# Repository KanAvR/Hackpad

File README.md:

# Hackpad

Hackpad is a 9 key macropad with a rotary encoder, an OLED Display and uses KMK firmware.

This will be used as a macropad for common desktop shortcuts such as, switching desktops; To boost productivity.

## Features:
- Open case because it looks cool
- 128x32 OLED Display
- EC11 Rotary encoder.
- 1 SK6812 MINI-E LED. 
- 9 Keys

## CAD Model:
Made in Blender.
The model is made of two seprate parts that will be screwed togeather to make the case.

## PCB
Made in KiCAD.
Schematic

PCB

## Firmware Overview
This hackpad uses KMK firmware.
 
- The rotary encoder changes volume. Turning it clockwise increases the volume by 5% and turning it counter-clockwise decreases it by 5%. Pressing it toggles mute.
- The 9 keys will be bound to various hyprland shortcuts as and when required. Right now key 1-6 switch to workspaces 1-6, key 7 kills the focused window, key 8 toggles fullscreen, and key 9 takes a screenshot.
- The OLED will be used for showing volume status. It shows a bar that fills up as the volume increases and shows MUTE when muted.
- The SK6812MINI LED glows blue normally and turns red when muted.

## BOM:
| Name | Purpose | Qty | Price | Link | Distributor |
|------|---------|-----|-------------|------|-------------|
| 0.91 inch blue OLED display module | Volume display (I already have this) | 1 | 0.00 | [Link](https://robocraze.com/products/0-91-inch-blue-oled-display-module) | Robo Craze |
| SK6812 MINI E RGB LED 3228 SMD Individually Addressable Full Color DC 5V (Pack of 100) | Mute status indicator (I already have this) | 1 | 0.00 | [Link](https://www.amazon.in/100PCS-Similar-WS2812B-Individually-Addressable/dp/B0DMNBBM9V) | Amazon |
| 1N4148 Fast Switching Diodes, 100V 300mA, Pack of 100, DO 35 Glass Zener Diodes for Electronic Projects | Preventing Ghosting (quantity is 1 because it comes in packs of 100, I will use 9) (I already have this) | 1 | 0.00 | [Link](https://www.amazon.in/100-Pieces-1N4148-Switching-High-Speed/dp/B079KJ91JZ) | Amazon |
| CentIoT EC11 10K Rotary Encoder Digital Potentiometer Coding Volume Control with switch 5 Pin 15mm Half handle (2PCS) | Volume knob (I already have this) | 1 | 0.00 | [Link](https://www.amazon.in/CentIoT-Encoder-Digital-Potentiometer-Control/dp/B0888RWNM1) | Amazon |
| Seeed Studio XIAO RP2040 Development Board | Connecting the hackpad to my computer (I already have this) | 1 | 0.00 | [Link](https://robocraze.com/products/seeed-studio-xiao-rp2040-development-board) | Robo Craze |
| Cherry MX Switches | Mechanical key switches (got from an old keyboard that stopped working) | 9 | 0.00 | N/A | N/A |
| DSA Keycaps | Keycaps for switches (got from an old keyboard that stopped working) | 9 | 0.00 | N/A | N/A |

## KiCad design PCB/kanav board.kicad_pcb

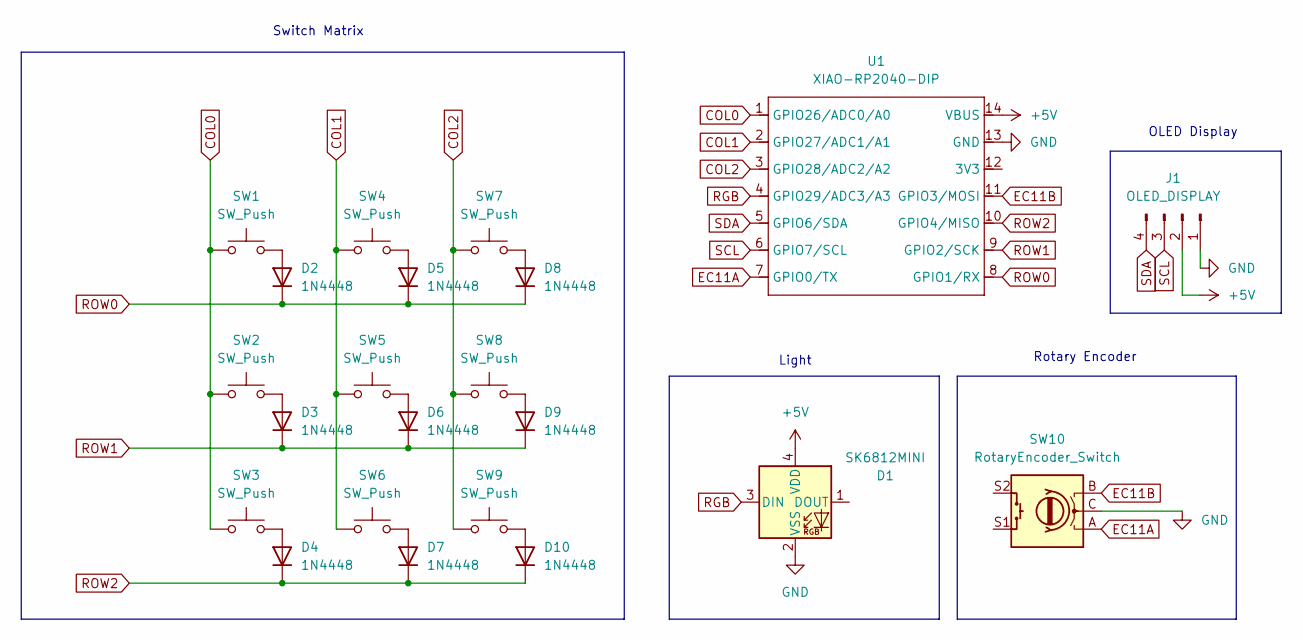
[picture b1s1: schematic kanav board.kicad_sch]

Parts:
D1: SK6812MINI; LED_SK6812MINI_PLCC4_3.5x3.5mm_P1.75mm
D2, D3, D4, D5, D6, D7, D8, D9, D10: 1N4448; D_DO-35_SOD27_P7.62mm_Horizontal
J1: OLED_DISPLAY; SSD1306-0.91-OLED-4pin-128x32
SW1, SW2, SW3, SW4, SW5, SW6, SW7, SW8, SW9: SW_Push; SW_Cherry_MX_1.00u_PCB
SW10: RotaryEncoder_Switch; RotaryEncoder_Alps_EC11E-Switch_Vertical_H20mm
U1: XIAO-RP2040-DIP

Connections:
+5V: D1.4 (VDD), J1.2, U1.14 (VBUS)
COL0: SW1.1, SW2.1, SW3.1, U1.1 (GPIO26/ADC0/A0)
COL1: SW4.1, SW5.1, SW6.1, U1.2 (GPIO27/ADC1/A1)
COL2: SW7.1, SW8.1, SW9.1, U1.3 (GPIO28/ADC2/A2)
EC11A: SW10.A, U1.7 (GPIO0/TX)
EC11B: SW10.B, U1.11 (GPIO3/MOSI)
GND: D1.2 (VSS), J1.1, SW10.C, U1.13 (GND)
unnamed: D2.2 (A), SW1.2
unnamed: D3.2 (A), SW2.2
unnamed: D4.2 (A), SW3.2
unnamed: D5.2 (A), SW4.2
unnamed: D6.2 (A), SW5.2
unnamed: D7.2 (A), SW6.2
unnamed: D8.2 (A), SW7.2
unnamed: D9.2 (A), SW8.2
unnamed: D10.2 (A), SW9.2
RGB: D1.3 (DIN), U1.4 (GPIO29/ADC3/A3)
ROW0: D2.1 (K), D5.1 (K), D8.1 (K), U1.8 (GPIO1/RX)
ROW1: D3.1 (K), D6.1 (K), D9.1 (K), U1.9 (GPIO2/SCK)
ROW2: D4.1 (K), D7.1 (K), D10.1 (K), U1.10 (GPIO4/MISO)
SCL: J1.3, U1.6 (GPIO7/SCL)
SDA: J1.4, U1.5 (GPIO6/SDA)

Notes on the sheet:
OLED Display
Light
Rotary Encoder
Switch Matrix

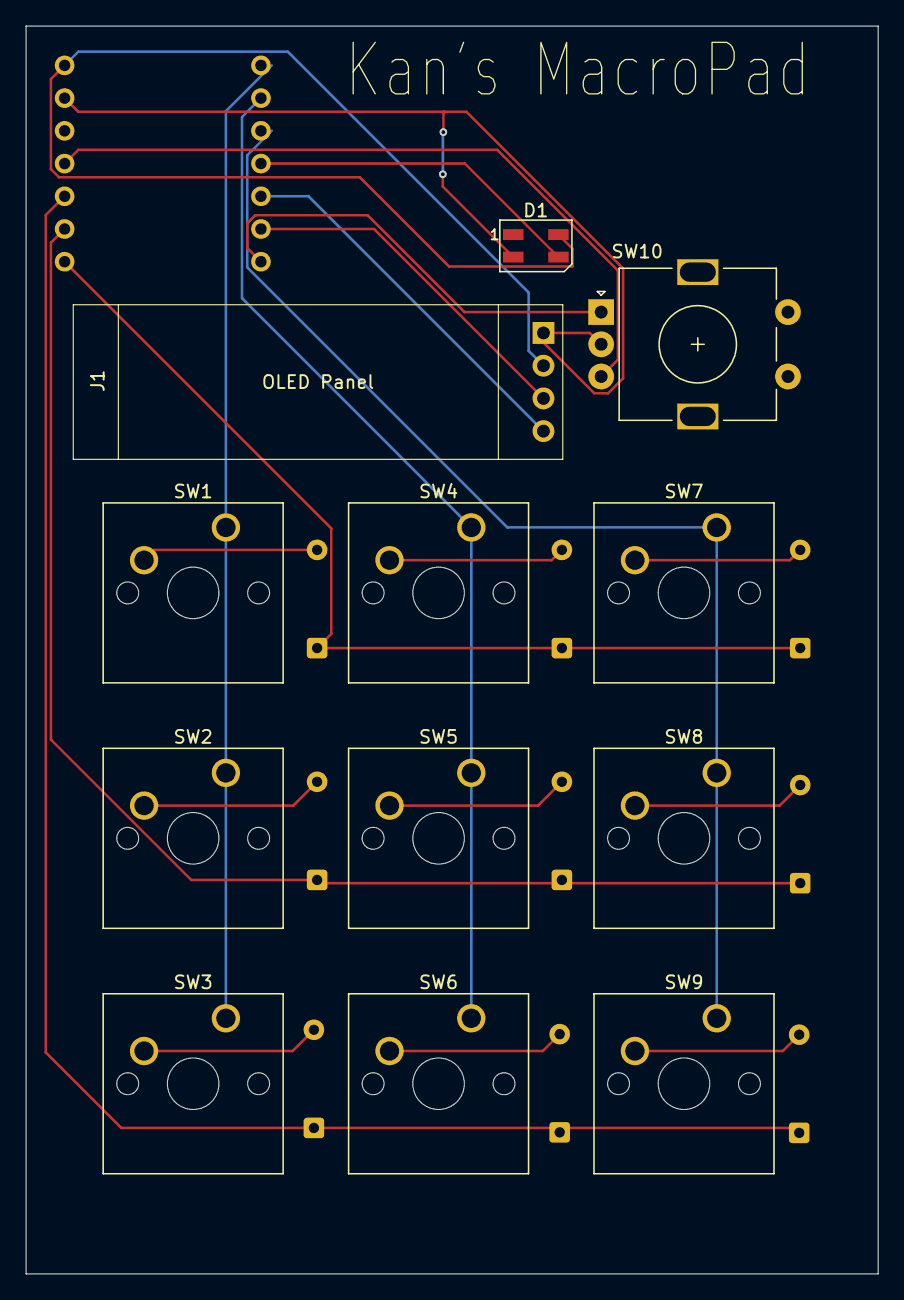
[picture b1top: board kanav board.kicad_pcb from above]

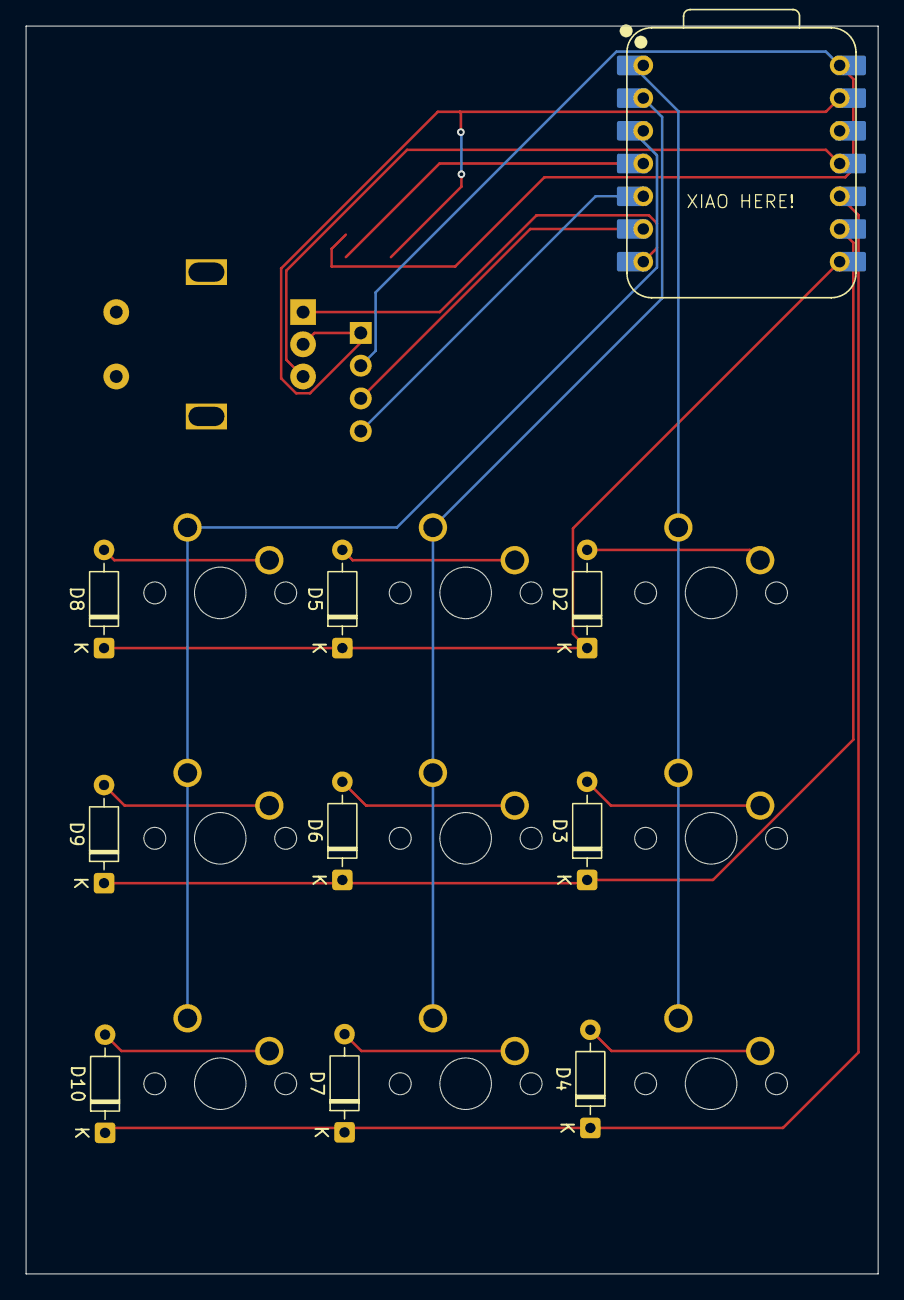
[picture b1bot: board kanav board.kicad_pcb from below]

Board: 2 copper layers, 66.1 x 96.9 mm, 22 parts (10 on the bottom side), 22 nets.

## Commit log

2026-03-29 added files
2026-03-29 Add README.md
    Added detailed information about the Hackpad project, including features, CAD model, PCB details, firmware overview, and bill of materials.
2026-03-29 formating
    Added PCB image section to the README.
2026-03-29 Change PCB image width to 500 pixels
    Updated PCB image size in README
2026-03-29 changed cad image
2026-03-29 added firmware to production
2026-03-29 added firmware folder
2026-03-29 firmware info updates
2026-04-22 Create CAD
2026-04-22 Change CAD model creation tool from Fusion to Blender
    Updated CAD model description and image source.
2026-04-22 Rename assets/CleanShot 2026-04-22 at 20.04.34@2x.png to cad.png
2026-04-24 Add files via upload
    fixed scaling issue with the 3d model
2026-04-24 fixed base scaling issue
2026-04-26 Add files via upload
    added step files and added the missing led hole
2026-04-26 Update LED description for mute status indicator
2026-04-26 Update BOM prices to remove dollar signs
